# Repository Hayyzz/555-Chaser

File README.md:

Hello !

This is my first project for PCB Design, A 555 timer + 4017 LED Chaser

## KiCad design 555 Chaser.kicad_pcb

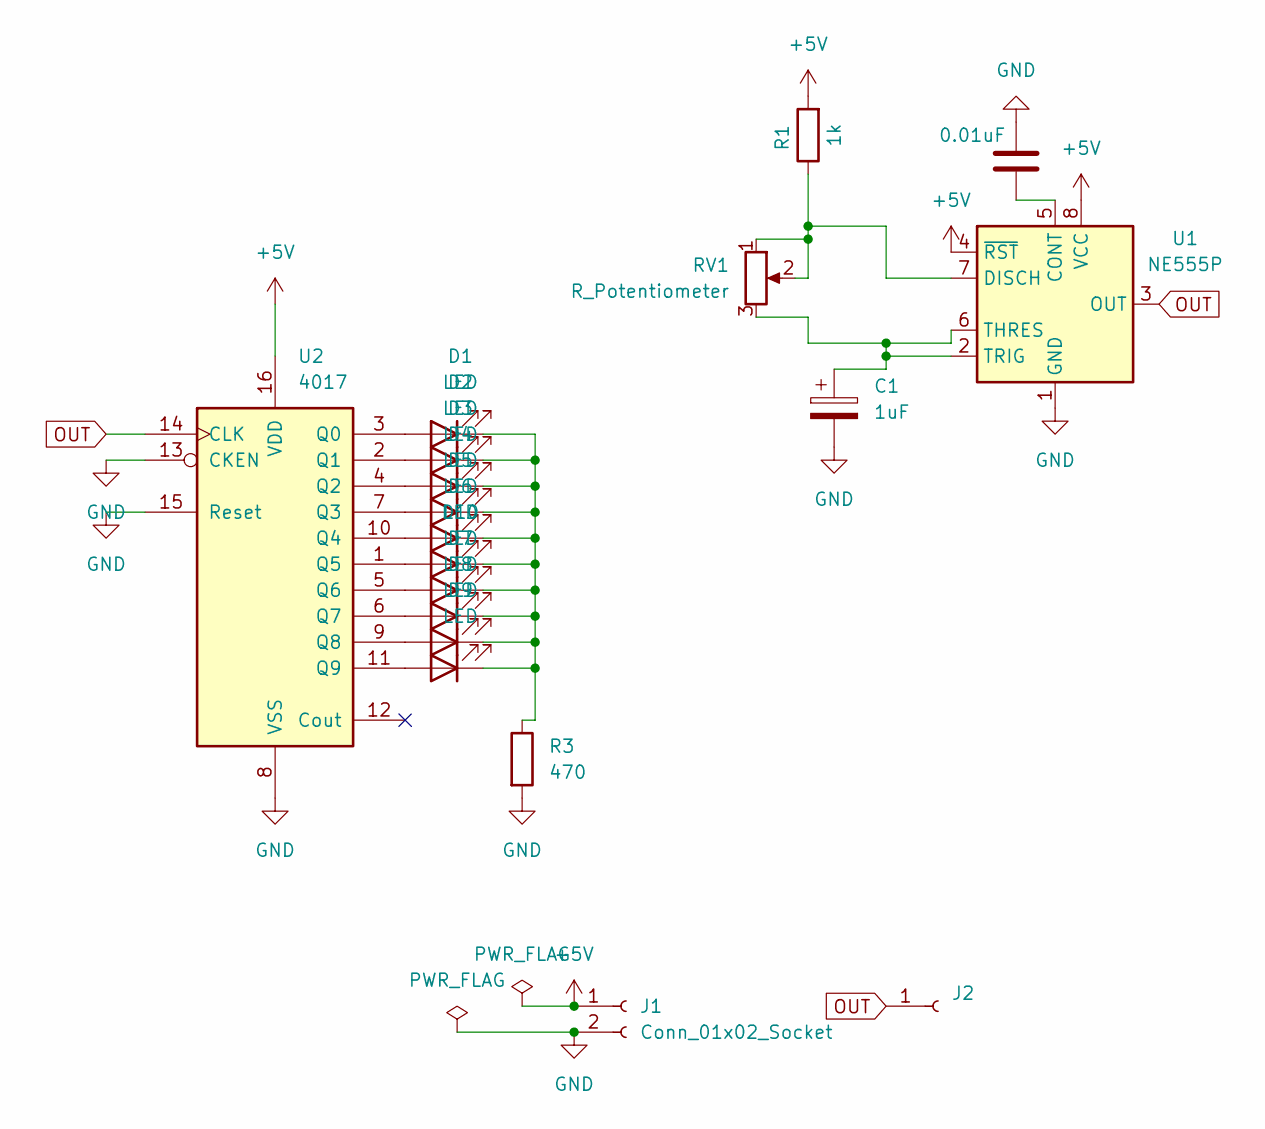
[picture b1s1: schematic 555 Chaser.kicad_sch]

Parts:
C1: 1uF; CP_Radial_D5.0mm_P2.00mm
C2: 0.01uF; C_Disc_D7.5mm_W2.5mm_P5.00mm
D1, D2, D3, D4, D5, D6, D7, D8, D9, D10: LED; LED_D3.0mm
J1: Conn_01x02_Socket; PinHeader_1x02_P2.54mm_Vertical
J2: Conn_01x01_Socket; PinHeader_1x01_P2.54mm_Vertical
R1: 1k; R_Axial_DIN0207_L6.3mm_D2.5mm_P7.62mm_Horizontal
R3: 470; R_Axial_DIN0207_L6.3mm_D2.5mm_P7.62mm_Horizontal
RV1: R_Potentiometer; Potentiometer_Vishay_T93YA_Vertical
U1: NE555P; DIP-8_W7.62mm
U2: 4017; N16

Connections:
+5V: J1.1, R1.2, U1.4 (~RST), U1.8 (VCC), U2.16 (VDD)
GND: C1.2, C2.1, J1.2, R3.2, U1.1 (GND), U2.8 (VSS), U2.13 (CKEN), U2.15 (Reset)
unnamed: D1.2 (A), U2.3 (Q0)
unnamed: D1.1 (K), D2.1 (K), D3.1 (K), D4.1 (K), D5.1 (K), D6.1 (K), D7.1 (K), D8.1 (K), D9.1 (K), D10.1 (K), R3.1
unnamed: D2.2 (A), U2.2 (Q1)
unnamed: D3.2 (A), U2.4 (Q2)
unnamed: D4.2 (A), U2.7 (Q3)
unnamed: D5.2 (A), U2.10 (Q4)
unnamed: D6.2 (A), U2.1 (Q5)
unnamed: D7.2 (A), U2.6 (Q7)
unnamed: D8.2 (A), U2.9 (Q8)
unnamed: D9.2 (A), U2.11 (Q9)
unnamed: D10.2 (A), U2.5 (Q6)
unnamed: C2.2, U1.5 (CONT)
unnamed: R1.1, RV1.1, RV1.2, U1.7 (DISCH)
unnamed: C1.1, RV1.3, U1.2 (TRIG), U1.6 (THRES)
OUT: J2.1 (Pin_1_1), U1.3 (OUT), U2.14 (CLK)

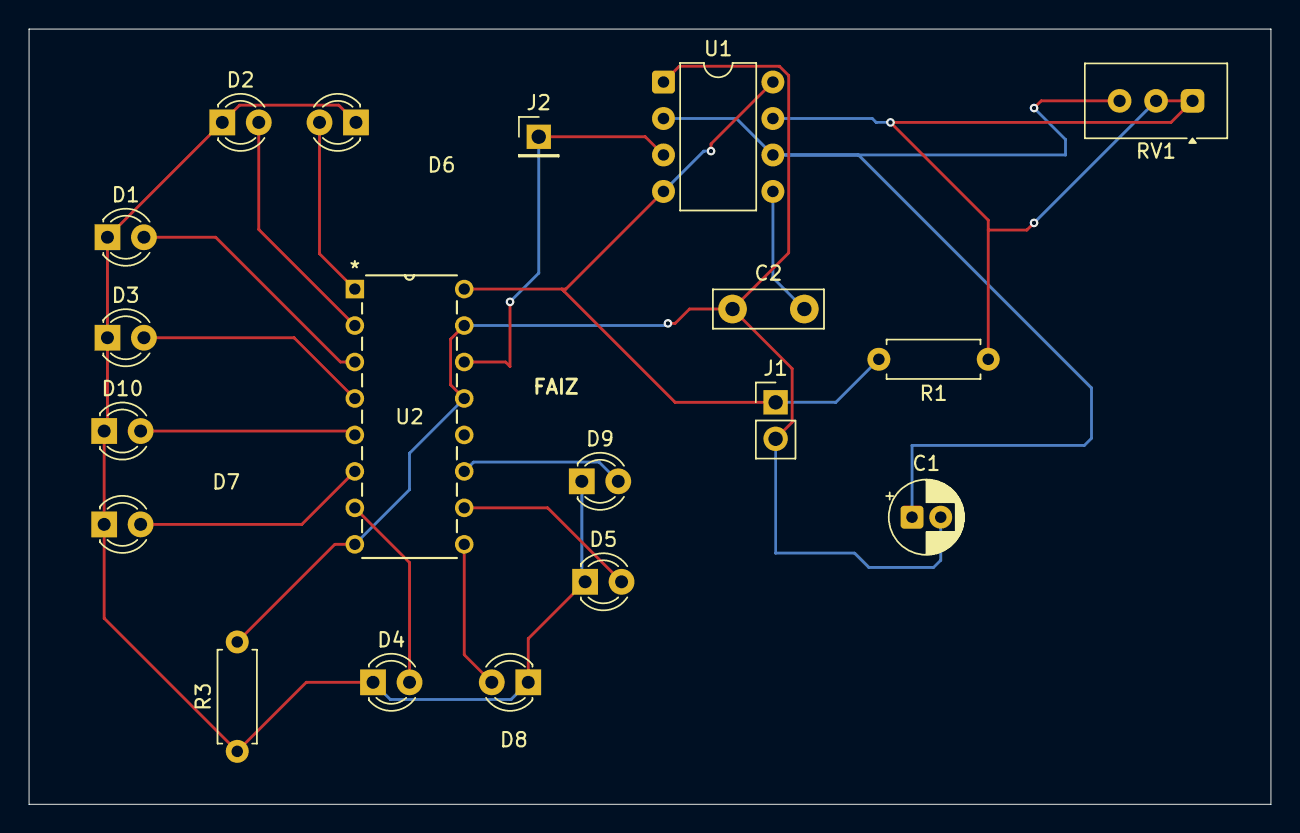
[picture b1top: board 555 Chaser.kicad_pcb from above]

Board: 2 copper layers, 86.5 x 54.0 mm, 19 parts (0 on the bottom side), 17 nets.
